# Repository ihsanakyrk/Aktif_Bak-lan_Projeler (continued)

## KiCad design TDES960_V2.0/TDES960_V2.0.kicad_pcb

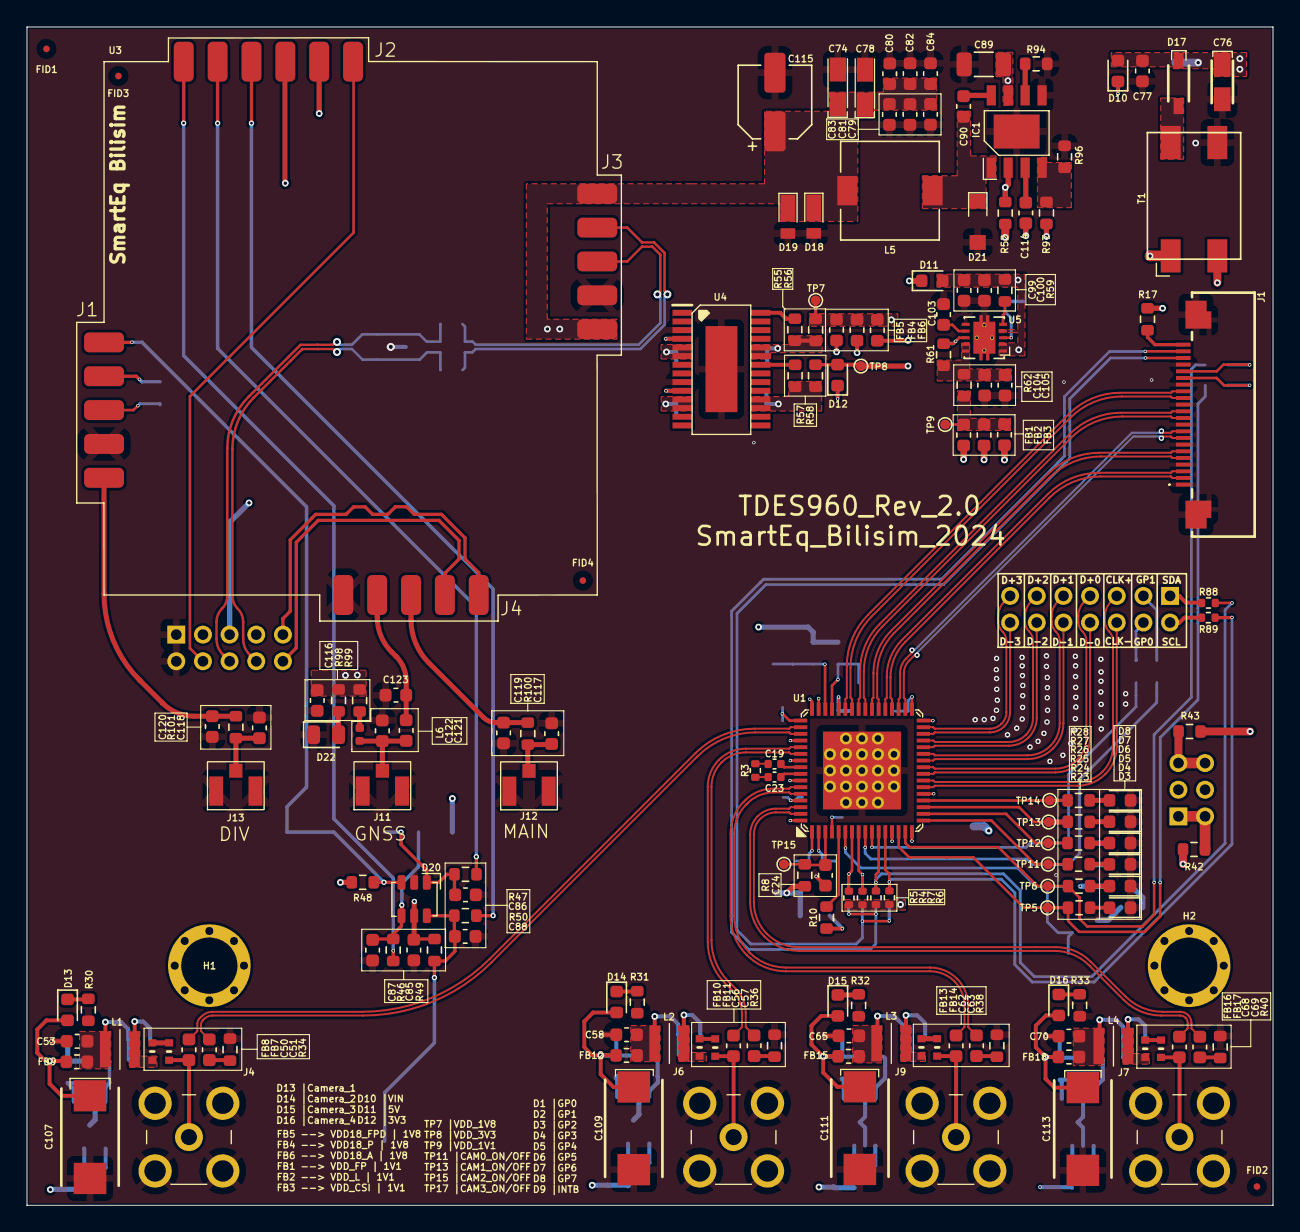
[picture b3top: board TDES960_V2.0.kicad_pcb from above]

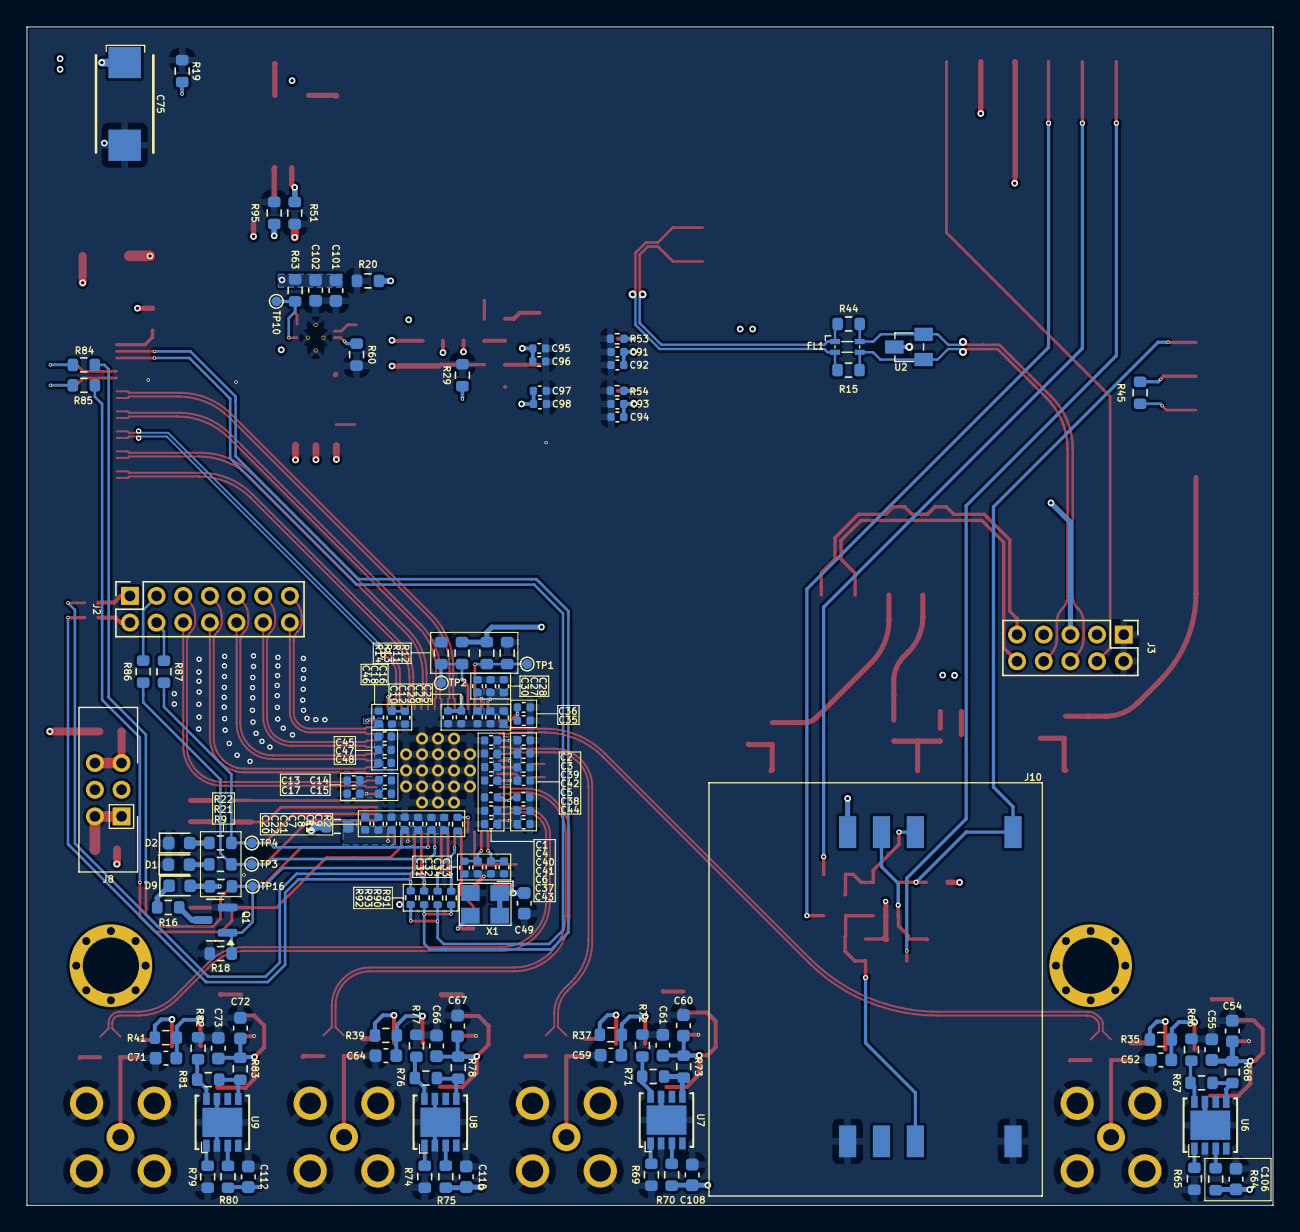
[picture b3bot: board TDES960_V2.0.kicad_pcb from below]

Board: 4 copper layers, 93.5 x 88.4 mm, 318 parts (149 on the bottom side), 184 nets.

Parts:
C1, C6, C11, C12, C17, C18, C22, C26, C29, C31, C33, C35, C39, C41, C43, C45: 0.01uF; C_0402_1005Metric
C2, C5, C9, C10, C15, C16, C19, C21, C23, C25, C30, C32, C34, C36, C40, C42, C44, C46, C95, C97: 0.1uF; C_0402_1005Metric
C3, C8, C14, C20, C28, C37, C47: 1uF; C_0402_1005Metric
C4, C7, C13, C27, C38, C48, C96, C98: 10uF; C_0402_1005Metric
C24, C105: 10uF; C_0603_1608Metric
C49, C83, C84, C85, C104, C116: 0.1uF; C_0603_1608Metric
C50, C56, C62, C68: 0.033uF/25V; C_0603_1608Metric
C51, C57, C63, C69: 0.015uF/25V; C_0603_1608Metric
C52, C54, C58, C60, C64, C66, C70, C72, C77: 0.1uF/25V; C_0603_1608Metric
C53, C55, C59, C61, C65, C67, C71, C73: 10uF/25V; C_0603_1608Metric
C74, C78: T490A107M006ATE500
C75, C107, C109, C111, C113: 22uF; CAPPM7343X310N
C76: 2.2uF; CAPPM3216X180N
C79, C80, C86, C87, C88: 33pF; C_0603_1608Metric
C81, C82: 10pF; C_0603_1608Metric
C89: 10uF; C_1206_3216Metric
C90: 100nF; C_0603_1608Metric
C91, C93: 4.7uF/10V; C_0402_1005Metric
C92, C94: 0.1uF/10V; C_0402_1005Metric
C99, C102: 4.7uF/10V; C_0603_1608Metric
C100: 0.1uF/10V; C_0603_1608Metric
C101: 1uF/10V; C_0603_1608Metric
C103: 0.01uF/10V; C_0603_1608Metric
C106, C108, C110, C112: 1uF/25V; C_0603_1608Metric
C114: 220pF; C_0603_1608Metric
C115: 100uF; CP_Elec_5x5.4
C117, C118, C119, C120, C121, C123: DNP; C_0603_1608Metric
C122: 100pF; C_0603_1608Metric
D1, D2, D3, D4, D5, D6, D7, D8, D9: LED_GREEN; LED_0603_1608Metric
D10, D11, D12: LED_RED; LED_0603_1608Metric
D13, D14, D15, D16: LED_ORANGE; LED_0603_1608Metric
D17: 1N5819HW-7-F; SOD3716X145N
D18, D19: TDZVTR5.1
D20: ESDA6V1-5SC6
D21: SS34FA
D22: LED_RED; LED_0805_2012Metric
FB1, FB2, FB3, FB4, FB5, FB6: 120ohm; 0603_Ferrite Beads
FB7, FB11, FB14, FB17: MPZ1005F470ETD25; BEADC1005X55N
FB8, FB10, FB13, FB16: MPZ1005S331ETD25; BEADC1005X55N
FB9, FB12, FB15, FB18: 1000ohm; 0603_Ferrite Beads
FID1, FID2, FID3, FID4: Fiducial; Fiducial_0.5mm_Mask1.5mm
FL1: ACM2012-900-2P-T002
H1, H2: M3x*0.5 L=6; Screw Terminal Shinbo
IC1: MP1584EN-LF-Z
J1: FFC SOCKET DR_BOTTOM 0.5MM -22P; F32R1A7H111022
J2: PinSocket_2x7_FEMALE_2.00mm; PinSocket_2x07_P2.00mm_Vertical
J3: FEMALE Through Hole Pin Header; PinHeader_2x05_P2.00mm_Vertical
J4, J6, J7, J9: XK1PWM13-ND24-Z
J8: PinSocket_2x3_FEMALE_2.00mm; Analog power connector
J10: 91228-3002; 912283002
J11, J12, J13: IPEX1-3-TXZ 214
L1, L2, L3, L4: LQH3NPN100MJR; LQH3NPN100MJRL
L5: 10uH; L_7.3x7.3_H3.5
L6: 47nH 5%; L_0402_1005Metric
Q1: BSS138; SOT-23
R1, R10, R17, R42, R43, R45, R56, R58, R62, R64, R68, R70, R73, R75, R78, R80, R83, R84, R85, R86, R87, R100, R101: 0R; R_0603_1608Metric
R2: 10K; R_0402_1005Metric
R3: 100R; R_0402_1005Metric
R4, R5, R6, R7: 4.7K; R_0402_1005Metric
R8, R12, R14, R19, R20, R29, R59: 10K; R_0603_1608Metric
R9: 4.7K; R_0603_1608Metric
R11, R13, R15, R44: DNP; R_0603_1608Metric
R16, R30, R31, R32, R33: 470R; R_0603_1608Metric
R18, R52, R55, R57, R63: 100K; R_0603_1608Metric
R21, R22, R23, R24, R25, R26, R27, R28: 220R; R_0603_1608Metric
R34, R36, R38, R40: 49.9R / %1; R_0603_1608Metric
R35, R37, R39, R41: 4.02K; R_0603_1608Metric
R46, R47, R50: 22R; R_0603_1608Metric
R48: 51K; R_0603_1608Metric
R49: 15K; R_0603_1608Metric
R51: 24.9K; R_0603_1608Metric
R53, R54, R88, R89, R90, R91: 0R; R_0402_1005Metric
R60: 4.99K/%1; R_0603_1608Metric
R61: 1.87K/%1; R_0603_1608Metric
R65, R69, R74, R79: 3.24K; R_0603_1608Metric
R66, R72, R77, R82: 5.6K/%1; R_0603_1608Metric
R67, R71, R76, R81: 34.0K/%1; R_0603_1608Metric
R92, R93: DNP; R_0402_1005Metric
R94: 200K; R_0603_1608Metric
R95: 68.1K; R_0603_1608Metric
R96: 40.2K; R_0603_1608Metric
R97: 150K; R_0603_1608Metric
R98: 1K; R_0603_1608Metric
R99: 10R; R_0603_1608Metric
T1: ACM9070-701-2PL-TL01; ACM9070
TP1, TP2, TP3, TP4, TP5, TP6, TP7, TP8, TP9, TP10, TP11, TP12, TP13, TP14, TP15, TP16: DNP; TestPoint_Pad_D0.75
U1: TDES960RTDR; QFN50P900X900X90-65N-D
U2: TPET05US3
U3: DNP; GSM_Castelled
U4: TPS767D318PWP; SOP65P640X120-29N
U5: TPS74801TDRCRQ1; VREG_TPS74801TDRCRQ1
U6, U7, U8, U9: LM2941LD_NOPB; DFN400X400X80-9N
X1: 25MHZ/100ppm/Oscillator; SMD3225-4P

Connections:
/+3V8: C74.1, C78.1, C79.1, C80.1, C81.1, C82.1, C83.1, C84.1, C115.1, C116.1, D18.1 (K), D19.1 (K), L5.2, R97.2, R98.2, R99.1, U3.17 (+3V8), U3.21 (+3V8)
/ALL_3: J8.5, J8.6, R43.2
/ALL_5: J8.1, J8.2, R42.2
/ALL_12: J8.3, T1.1IN
/ANT_DIV: C120.1, R101.2, U3.6 (ANT_DIV)
/ANT_GNSS: C122.2, C123.1, U3.4 (ANT_GNSS)
/ANT_MAIN: C119.1, R100.2, U3.3 (ANT_MAIN)
/CMLOUT_N: C23.1, R3.1
/CMLOUT_P: C19.1, R3.2
/CSI0_CLKN: J2.6, U1.22 (CSI0_CLKN)
/CSI0_CLKP: J2.5, U1.23 (CSI0_CLKP)
/CSI0_D0N: J2.8, U1.24 (CSI0_D0N)
/CSI0_D0P: J2.7, U1.25 (CSI0_D0P)
/CSI0_D1N: J2.10, U1.26 (CSI0_D1N)
/CSI0_D1P: J2.9, U1.27 (CSI0_D1P)
/CSI0_D2N: J2.12, U1.28 (CSI0_D2N)
/CSI0_D2P: J2.11, U1.29 (CSI0_D2P)
/CSI0_D3N: J2.14, U1.30 (CSI0_D3N)
/CSI0_D3P: J2.13, U1.31 (CSI0_D3P)
/CSI1_CLKN: J1.8, U1.34 (CSI1_CLKN)
/CSI1_CLKP: J1.9, U1.35 (CSI1_CLKP)
/CSI1_D0N: J1.2, U1.36 (CSI1_D0N)
/CSI1_D0P: J1.3, U1.37 (CSI1_D0P)
/CSI1_D1N: J1.5, U1.38 (CSI1_D1N)
/CSI1_D1P: J1.6, U1.39 (CSI1_D1P)
/CSI1_D2N: J1.11, U1.40 (CSI1_D2N)
/CSI1_D2P: J1.12, U1.41 (CSI1_D2P)
/CSI1_D3N: J1.14, U1.42 (CSI1_D3N)
/CSI1_D3P: J1.15, U1.43 (CSI1_D3P)
/EN3V8: IC1.2 (EN), J3.5, R51.1, R52.2
/GPIO0: R21.1, R86.1, TP3.1, U1.9 (GPIO0)
/GPIO1: R22.1, R87.1, TP4.1, U1.10 (GPIO1)
/GPIO2: R23.1, R84.1, TP5.1, U1.14 (GPIO2)
/GPIO3: R24.1, R85.1, TP6.1, U1.15 (GPIO3)
/GPIO4: R25.1, TP11.1, U1.17 (GPIO4)
/GPIO5: R26.1, TP12.1, U1.18 (GPIO5)
/GPIO6: R27.1, TP13.1, U1.19 (GPIO6)
/GPIO7: R28.1, TP14.1, U1.20 (GPIO7)
/I2C_SCL1: R4.1, R90.1, U1.8 (I2C_SCL2)
/I2C_SDA1: R5.1, R91.1, U1.7 (I2C_SDA2)
/IDX: R11.2, R12.1, TP1.1, U1.46 (IDX)
/INTB: Q1.1 (G), R9.2, R18.1, TP16.1, U1.6 (INTB)
/MODE: R13.2, R14.1, TP2.1, U1.45 (MODE)
/MODEM_NET_STATUS: J3.4, U3.16 (MODEM+NET+STATUS)
/PDB: C24.2, R8.1, TP15.1, U1.3 (PDB)
/RES: R2.2, U1.4 (RES)
/RIN0+: C50.2, U1.50 (RIN0+)
/RIN0-: C51.2, U1.51 (RIN0-)
/RIN1+: C56.2, U1.53 (RIN1+)
/RIN1-: C57.2, U1.54 (RIN1-)
/RIN2+: C62.2, U1.59 (RIN2+)
/RIN2-: C63.2, U1.60 (RIN2-)
/RIN3+: C68.2, U1.62 (RIN3+)
/RIN3-: C69.2, U1.63 (RIN3-)
/RXD: J3.10, U3.2 (RXD)
/SCL: R6.1, R89.1, R92.1, U1.12 (I2C_SCL)
/SDA: R7.1, R88.1, R93.1, U1.11 (I2C_SDA)
/TXD: J3.9, U3.1 (TXD)
/USB_GSM_N: FL1.3, J3.8, R15.1, U2.1
/USB_GSM_P: FL1.4, J3.6, R44.2, U2.2
/USB_N: FL1.2, R15.2, U3.18 (USB_N)
/USB_P: FL1.1, R44.1, U3.19 (USB_P)
/USIM_CLK: R47.1, U3.12 (USIM_CLK)
/USIM_DATA: R50.1, U3.13 (USIM_DATA)
/USIM_PRESENCE: D20.3, J10.8 (PRESENCE), R48.1, U3.10 (USIM_PRESENCE)
/USIM_RST: R46.1, U3.11 (USIM_RST)
/USIM_VDD: C85.1, D20.5, J10.6 (VCC), R49.1, U3.14 (USIM_VDD)
/VDD_EXT_1V8: R48.2, U3.15 (VDD_EXT_1V8)
/VIN: C89.1, IC1.7 (VIN), J3.3, J3.7, R52.1
/XCLK_25MHz: R10.1, U1.5 (REFCLK)
GND: C1.2, C2.2, C3.2, C4.2, C5.2, C6.2, C7.2, C8.2, C9.2, C10.2, C11.2, C12.2, C13.2, C14.2, C15.2, C16.2, C17.2, C18.2, C20.2, C21.2, C22.2, C24.1, C25.2, C26.2, C27.2, C28.2, C29.2, C30.2, C31.2, C32.2, C33.2, C34.2, C35.2, C36.2, C37.2, C38.2, C39.2, C40.2, C41.2, C42.2, C43.2, C44.2, C45.2, C46.2, C47.2, C48.2, C49.2, C52.1, C53.1, C54.1, C55.1, C58.1, C59.1, C60.1, C61.1, C64.1, C65.1, C66.1, C67.1, C70.1, C71.1, C72.1, C73.1, C74.2, C75.2, C76.2, C77.1, C78.2, C79.2, C80.2, C81.2, C82.2, C83.2, C84.2, C85.2, C86.2, C87.2, C88.2, C89.2, C91.1, C92.1, C93.1, C94.1, C95.1, C96.1, C97.1, C98.1, C99.1, C100.1, C101.1, C102.1, C103.1, C104.1, C105.1, C106.2, C107.2, C108.2, C109.2, C110.2, C111.2, C112.2, C113.2, C115.2, C116.2, C117.1, C118.1, C119.2, C120.2, C121.1, C123.2, D1.1 (K), D2.1 (K), D3.1 (K), D4.1 (K), D5.1 (K), D6.1 (K), D7.1 (K), D8.1 (K), D18.2 (A), D19.2 (A), D20.2, D21.2 (A), D22.1 (K), IC1.5 (GND), IC1.9 (EP), J1.1, J1.4, J1.7, J1.10, J1.13, J1.16, J1.19, J1.23, J1.24, J3.1, J3.2, J4.2, J4.3, J4.4, J4.5, J6.2, J6.3, J6.4, J6.5, J7.2, J7.3, J7.4, J7.5, J9.2, J9.3, J9.4, J9.5, J10.1 (GND), J10.7 (NC), J11.2, J11.3, J12.2, J12.3, J13.2, J13.3, Q1.2 (S), R2.1, R12.2, R14.2, R18.2, R19.2, R20.2, R29.2, R30.2, R31.2, R32.2, R33.2, R34.1, R36.1, R38.1, R40.1, R51.2, R53.2, R54.2, R60.2, R65.1, R66.2, R69.1, R72.2, R74.1, R77.2, R79.1, R82.2, R94.2, R95.2, R96.2, T1.2OUT, U1.65 (DAP), U2.3, U3.5 (GND), U3.7 (GND), U3.20 (GND), U4.3 (1GND), U4.9 (2GND), U4.29 (EP), U5.6 (GND), U5.11 (EXP), U6.2 (GND_2), U6.7 (GND_3), U6.9 (GND), U7.2 (GND_2), U7.7 (GND_3), U7.9 (GND), U8.2 (GND_2), U8.7 (GND_3), U8.9 (GND), U9.2 (GND_2), U9.7 (GND_3), U9.9 (GND), X1.2 (GND)
unnamed: C50.1, FB7.1, J4.1
unnamed: C51.1, R34.2
unnamed: C52.2, C53.2, FB9.2, L1.2, R35.2
unnamed: C56.1, FB11.1, J6.1
unnamed: C57.1, R36.2
unnamed: C58.2, C59.2, FB12.2, L2.2, R37.2
unnamed: C62.1, FB14.1, J9.1
unnamed: C63.1, R38.2
unnamed: C64.2, C65.2, FB15.2, L3.2, R39.2
unnamed: C68.1, FB17.1, J7.1
unnamed: C69.1, R40.2
unnamed: C70.2, C71.2, FB18.2, L4.2, R41.2
unnamed: C95.2, C96.2, R55.1, R56.2, U4.23 (1OUT), U4.24 (1OUT)
unnamed: C97.2, C98.2, R57.1, R58.2, U4.17 (2OUT), U4.18 (2OUT)
unnamed: C104.2, C105.2, R61.2, R62.2, U5.9 (OUT), U5.10 (OUT)
unnamed: C114.2, R95.1
unnamed: D1.2 (A), R21.2
unnamed: D2.2 (A), R22.2
unnamed: D3.2 (A), R23.2
unnamed: D4.2 (A), R24.2
unnamed: D5.2 (A), R25.2
unnamed: D6.2 (A), R26.2
unnamed: D7.2 (A), R27.2
unnamed: D8.2 (A), R28.2
unnamed: D9.1 (K), R16.1
unnamed: D10.1 (K), R19.1
unnamed: D11.1 (K), R20.1
unnamed: D12.1 (K), R29.1
unnamed: D13.1 (K), R30.1
unnamed: D14.1 (K), R31.1
unnamed: D15.1 (K), R32.1
unnamed: D16.1 (K), R33.1
unnamed: D17.2 (A), T1.1OUT
unnamed: C90.2, D21.1 (K), IC1.1 (SW), L5.1
unnamed: D22.2 (A), R98.1
unnamed: FB7.2, FB8.1
unnamed: FB8.2, L1.1, R35.1
unnamed: FB10.1, FB11.2
unnamed: FB10.2, L2.1, R37.1
unnamed: FB13.1, FB14.2
unnamed: FB13.2, L3.1, R39.1
unnamed: FB16.1, FB17.2
unnamed: FB16.2, L4.1, R41.1
unnamed: C90.1, IC1.8 (BST)
unnamed: C114.1, IC1.3 (COMP)
unnamed: IC1.4 (FB), R96.1, R97.1
unnamed: IC1.6 (FREQ), R94.1
unnamed: J1.17, R84.2
unnamed: J1.18, R85.2
unnamed: J1.20, R90.2, R92.2
unnamed: J1.21, R91.2, R93.2
unnamed: J1.22, R17.2
unnamed: J2.1, R88.2
unnamed: J2.2, R89.2
unnamed: J2.3, R86.2
unnamed: J2.4, R87.2
unnamed: J8.4, T1.2IN
unnamed: C86.1, D20.1, J10.4 (CLK), R47.2
unnamed: C88.1, D20.6, J10.3 (I/O), R49.2, R50.2
unnamed: C87.1, D20.4, J10.5 (RST), R46.2
unnamed: C121.2, C122.1, J11.1, L6.2
unnamed: C117.2, J12.1, R100.1
unnamed: C118.2, J13.1, R101.1
unnamed: L6.1, R99.2
unnamed: Q1.3 (D), R16.2
unnamed: C19.2, U1.56 (CMLOUTP)
unnamed: C23.2, U1.57 (CNLOUTN)
unnamed: C29.1, C30.1, U1.47 (VDD18_P1)
unnamed: C31.1, C32.1, U1.2 (VDD18_P2)
unnamed: C33.1, C34.1, U1.1 (VDD18_P3)
unnamed: R45.1, U3.8 (CTS)
unnamed: R45.2, U3.9 (RTS)
unnamed: R53.1, U4.4 (~1EN)
unnamed: R55.2, U4.28 (~1RESET)
unnamed: R54.1, U4.10 (~2EN)
unnamed: R57.2, U4.22 (~2RESET)
unnamed: R59.1, U5.5 (EN)
unnamed: R60.1, R61.1, U5.8 (FB)
unnamed: R63.1, TP10.1, U5.3 (PG)
unnamed: C103.2, U5.7 (SS)
unnamed: R66.1, R67.2, U6.8 (ADJ)
unnamed: R64.2, U6.3 (IN)
unnamed: R65.2, U6.1 (ON/OFF)
unnamed: R67.1, R68.2, U6.5 (OUT)
unnamed: R71.2, R72.1, U7.8 (ADJ)
unnamed: R70.2, U7.3 (IN)
unnamed: R69.2, U7.1 (ON/OFF)
unnamed: R71.1, R73.2, U7.5 (OUT)
unnamed: R76.2, R77.1, U8.8 (ADJ)
unnamed: R75.2, U8.3 (IN)
unnamed: R74.2, U8.1 (ON/OFF)
unnamed: R76.1, R78.2, U8.5 (OUT)
unnamed: R81.2, R82.1, U9.8 (ADJ)
unnamed: R80.2, U9.3 (IN)
unnamed: R79.2, U9.1 (ON/OFF)
unnamed: R81.1, R83.2, U9.5 (OUT)
unnamed: R10.2, X1.3 (OUT)
VDD5V: C91.2, C92.2, C93.2, C94.2, C99.2, C100.2, C101.2, C102.2, D11.2 (A), R42.1, R59.2, R63.2, U4.5 (1IN), U4.6 (1IN), U4.11 (2IN), U4.12 (2IN), U5.1 (IN), U5.2 (IN), U5.4 (BIAS)
VDD18_A: C45.1, C46.1, C47.1, C48.1, FB6.1, U1.32 (VDD18A)
VDD18_FPD: C35.1, C36.1, C37.1, C38.1, C39.1, C40.1, C41.1, C42.1, C43.1, C44.1, FB5.1, U1.49 (VDD18_FPD0), U1.55 (VDD18_FPD1), U1.58 (VDD18_FPD2), U1.64 (VDD18_FPD3)
VDD18_P: C25.1, C26.1, C27.1, C28.1, FB4.1, U1.48 (VDD18_P0)
VDDIO: C20.1, C21.1, C22.1, R1.2, U1.16 (VDDIO)
VDD_1V1: FB1.1, FB2.1, FB3.1, R62.1, TP9.1
VDD_1V8: C49.1, FB4.2, FB5.2, FB6.2, R8.2, R11.1, R13.1, R56.1, TP7.1, X1.1 (ENABLE), X1.4 (VDD)
VDD_3V3: D9.2 (A), D12.2 (A), R1.1, R4.2, R5.2, R6.2, R7.2, R9.1, R17.1, R43.1, R58.1, TP8.1
VDD_CSI: C13.1, C14.1, C15.1, C16.1, C17.1, C18.1, FB3.2, U1.21 (VDD_CSI0), U1.33 (VDD_CSI1)
VDD_EXT: C75.1, C76.1, C77.2, C106.1, C108.1, C110.1, C112.1, D10.2 (A), D17.1 (K), R64.1, R70.1, R75.1, R80.1
VDD_FP: C1.1, C2.1, C3.1, C4.1, C5.1, C6.1, FB1.2, U1.52 (VDD_FPD1), U1.61 (VDD_FPD2)
VDD_L: C7.1, C8.1, C9.1, C10.1, C11.1, C12.1, FB2.2, U1.13 (VDDL1), U1.44 (VDDL2)
VPOC0: C54.2, C55.2, C107.1, D13.2 (A), FB9.1, R68.1
VPOC1: C60.2, C61.2, C109.1, D14.2 (A), FB12.1, R73.1
VPOC2: C66.2, C67.2, C111.1, D15.2 (A), FB15.1, R78.1
VPOC3: C72.2, C73.2, C113.1, D16.2 (A), FB18.1, R83.1

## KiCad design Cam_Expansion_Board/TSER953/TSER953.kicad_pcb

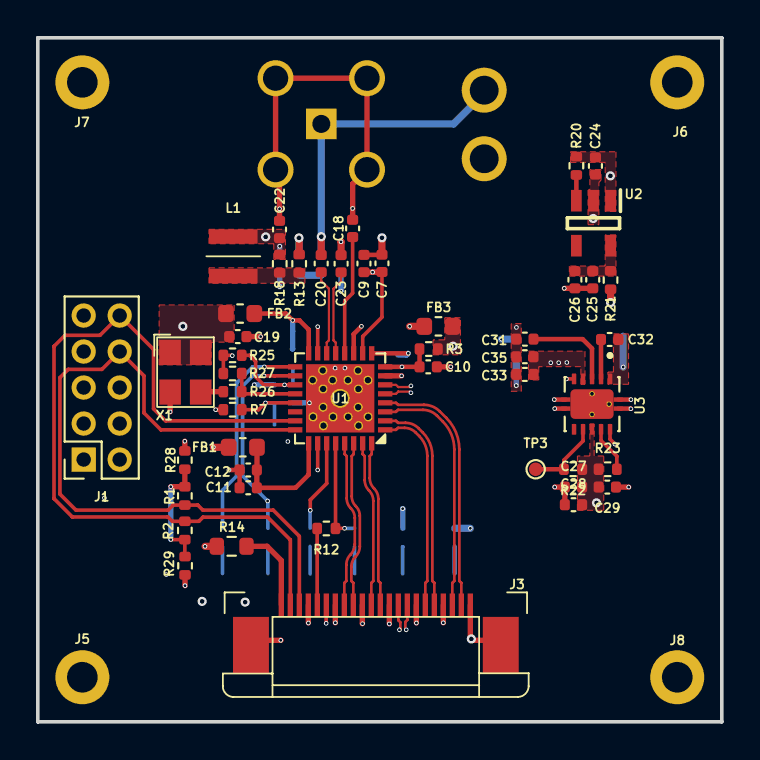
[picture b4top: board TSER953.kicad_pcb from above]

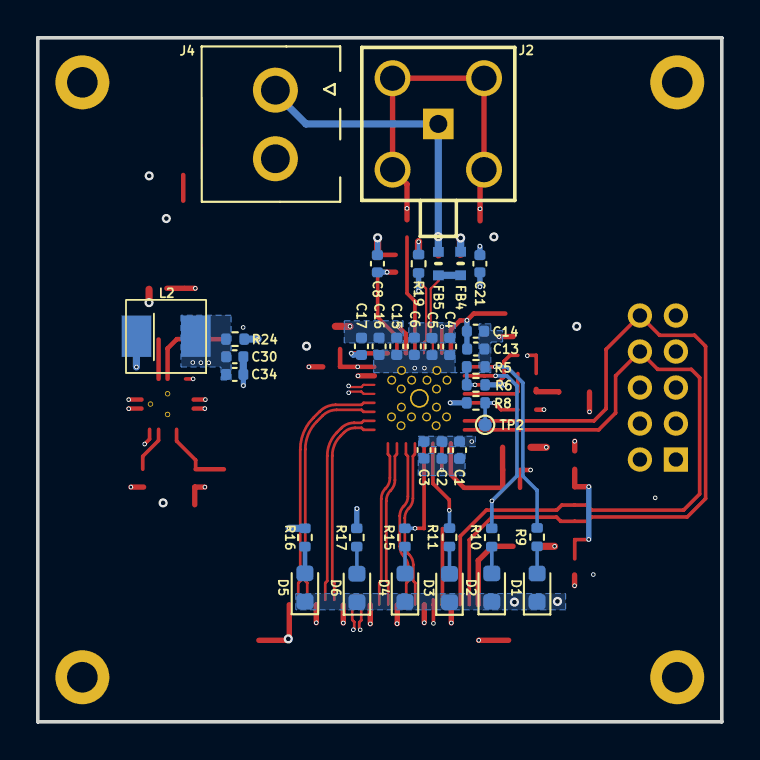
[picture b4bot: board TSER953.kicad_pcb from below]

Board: 6 copper layers, 38.0 x 38.0 mm, 90 parts (38 on the bottom side), 58 nets.

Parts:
C1, C5, C8, C10: 10uF; C_0402_1005Metric
C2, C6, C9, C12, C14, C16, C30: 0.01uF; C_0402_1005Metric
C3, C4, C7, C18, C19: 0.1uF; C_0402_1005Metric
C11, C13, C15: 1uF; C_0402_1005Metric
C17: 0.022uF; C_0402_1005Metric
C20: 0.033uF/25V; C_0402_1005Metric
C21, C22, C29, C32: 0.1uF/25V; C_0402_1005Metric
C23: 0.015uF/25V; C_0402_1005Metric
C24, C25: 1uF/10V; C_0402_1005Metric
C26, C33, C34: 10uF/10V; C_0402_1005Metric
C27: 10uF/25V; C_0402_1005Metric
C28: 4.7uF/25V; C_0402_1005Metric
C31: 1uF/25V; C_0402_1005Metric
C35: 22uF/10V; C_0402_1005Metric
D1, D2, D3, D4: LED_GREEN; LED_0603_1608Metric
D5: LED_RED; LED_0603_1608Metric
D6: LED_ORANGE; LED_0603_1608Metric
FB1, FB2, FB3: BLM18AG102SN1D; 0603_Ferrite Beads
FB4: MPZ1005S331ETD25; BEADC1005X55N
FB5: MPZ1005F470ETD25; BEADC1005X55N
J1: DNP; PinHeader_2x05_P2.00mm_Vertical
J2: 59S10H400T5Z
J3: FFC SOCKET DR_DWN 0.5MM -22P
J4: DNP; KF2EDGH-3.81-2P-Vertical
J5, J6, J7, J8: DNP; Screw
L1: LLQH3NPN100MJR; LQH3NPN100MJRL
L2: 4.7uH; MPI4040R3-4R7-R
R1, R2: 4.7K; R_0402_1005Metric
R3, R8, R16, R20, R22: 10K; R_0402_1005Metric
R5: 40.2K; R_0402_1005Metric
R6, R7, R25, R27, R29: DNP; R_0402_1005Metric
R9, R10, R11, R15: 220R; R_0402_1005Metric
R12, R13, R21, R24, R26, R28: 0R; R_0402_1005Metric
R14: 0R; R_0603_1608Metric
R17: 470R; R_0402_1005Metric
R18: 4.02K; R_0402_1005Metric
R19: 49.9R / %1; R_0402_1005Metric
R23: 100K; R_0402_1005Metric
TP2, TP3: DNP; TestPoint_Pad_D0.75
U1: TSER953RHBR; QFN50P500X500X100-33N-D
U2: LP5907MFX-1.8/NOPB; SOT95P280X145-5N
U3: LM536003QDSXRQ1; CONV_LM53600NQDSXTQ1
X1: 50MHZ/100ppm; SMD3225-4P

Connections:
/CSI_C_N: J3.15, U1.6 (CSI_CLKN)
/CSI_C_P: J3.14, U1.5 (CSI_CLKP)
/CSI_D0_N: J3.21, U1.4 (CSI_D0N)
/CSI_D0_P: J3.20, U1.3 (CSI_D0P)
/CSI_D1_N: J3.18, U1.2 (CSI_D1N)
/CSI_D1_P: J3.17, U1.1 (CSI_D1P)
/CSI_D2_N: J3.12, U1.32 (CSI_D2N)
/CSI_D2_P: J3.11, U1.31 (CSI_D2P)
/CSI_D3_N: J3.9, U1.30 (CSI_D3N)
/CSI_D3_P: J3.8, U1.29 (CSI_D3P)
/DOUT+: C20.1, U1.14 (DOUT+)
/DOUT-: C23.1, U1.13 (DOUT-)
/EXT_XVCLK: J3.6, R25.1, R27.2
/FSIN: J3.5, R12.2
/GPIO0: J1.7, R9.2, U1.17 (GPIO0)
/GPIO1: J1.5, R10.2, U1.18 (GPIO1)
/GPIO2: J1.3, R11.2, U1.27 (GPIO2)
/GPIO3: J1.1, R12.1, R15.2, U1.28 (GPIO3)
/I2C_SCL: J1.8, J3.3, R1.2, U1.24 (I2C_SCL)
/I2C_SDA: J1.10, J3.2, R2.2, U1.23 (I2C_SDA)
/IDX: R5.1, R6.2, R25.2, U1.19 (CLK_OUT/IDX)
/MODE: R7.2, R8.1, TP2.1, U1.21 (MODE)
/PDB: C10.2, J1.6, R3.1, U1.8 (PDB)
/XCLK_50MHz: R26.1, R27.1, U1.20 (CLKIN)
GND: C1.2, C2.2, C3.2, C4.2, C5.2, C6.2, C7.2, C8.2, C9.2, C10.1, C11.1, C12.2, C13.1, C14.2, C15.1, C16.2, C18.1, C19.2, C21.1, C22.1, C24.1, C25.1, C26.1, C27.1, C28.1, C29.1, C30.1, C31.1, C33.1, C34.1, C35.1, D1.1 (K), D2.1 (K), D3.1 (K), D4.1 (K), D5.1 (K), D6.1 (K), J1.4, J1.9, J2.2, J2.3, J2.4, J2.5, J3.4, J3.7, J3.10, J3.13, J3.16, J3.19, J3.22, J3.23, J3.24, J4.2, J5.1, J6.1, J7.1, J8.1, R5.2, R8.2, R19.2, U1.0 (DAP(GND)), U1.7 (RES0), U2.2 (GND), U3.5 (AGND), U3.10 (GND), U3.11 (PAD), X1.2 (GND)
unnamed: C23.2, R19.1
unnamed: D1.2 (A), R9.1
unnamed: D2.2 (A), R10.1
unnamed: D3.2 (A), R11.1
unnamed: D4.2 (A), R15.1
unnamed: D5.2 (A), R16.1
unnamed: D6.2 (A), R17.1
unnamed: FB4.1, FB5.2
unnamed: FB4.2, R13.2
unnamed: J3.1, R14.2
unnamed: C20.2, FB5.1, J2.1, J4.1
unnamed: L1.1, R13.1, R18.2
unnamed: R1.1, R2.1, R28.1, R29.1
unnamed: C17.1, U1.9 (LPF1)
unnamed: C18.2, U1.12 (LPF2)
unnamed: C7.1, C8.1, C9.1, U1.10 (VDDPLL_CAP)
unnamed: C4.1, C5.1, C6.1, U1.15 (VDDRV_CAP)
unnamed: C1.1, C2.1, C3.1, U1.26 (VDD_CAP)
unnamed: R20.2, U2.3 (EN)
unnamed: C25.2, C26.2, R21.1, U2.5 (OUT)
unnamed: C32.2, U3.2 (BOOT)
unnamed: R22.2, TP3.1, U3.7 (ENABLE)
unnamed: C30.2, C33.2, C34.2, C35.2, L2.2, R24.1, U3.4 (FB)
unnamed: C32.1, L2.1, U3.1 (SW)
unnamed: R23.2, U3.9 (SYNC/MODE)
unnamed: C31.2, U3.3 (VCC)
unnamed: R26.2, X1.3 (OUT)
VDDDRV_1V8: C13.2, C14.1, FB2.1, U1.16 (VDDDRV)
VDDD_1V8: C11.2, C12.1, FB1.1, U1.25 (VDDD)
VDD_1V8: C19.1, FB1.2, FB2.2, FB3.2, R3.2, R6.1, R7.1, R21.2, R28.2, X1.1 (ENABLE), X1.4 (VDD)
VDD_3V3: C24.2, J1.2, R14.1, R16.2, R20.1, R24.2, R29.2, U2.1 (VIN)
VDD_PLL: C15.2, C16.1, C17.2, FB3.1, U1.11 (VDDPLL)
VPOC: C21.2, C22.2, C27.2, C28.2, C29.2, L1.2, R17.2, R18.1, R22.1, R23.1, U3.8 (VIN)

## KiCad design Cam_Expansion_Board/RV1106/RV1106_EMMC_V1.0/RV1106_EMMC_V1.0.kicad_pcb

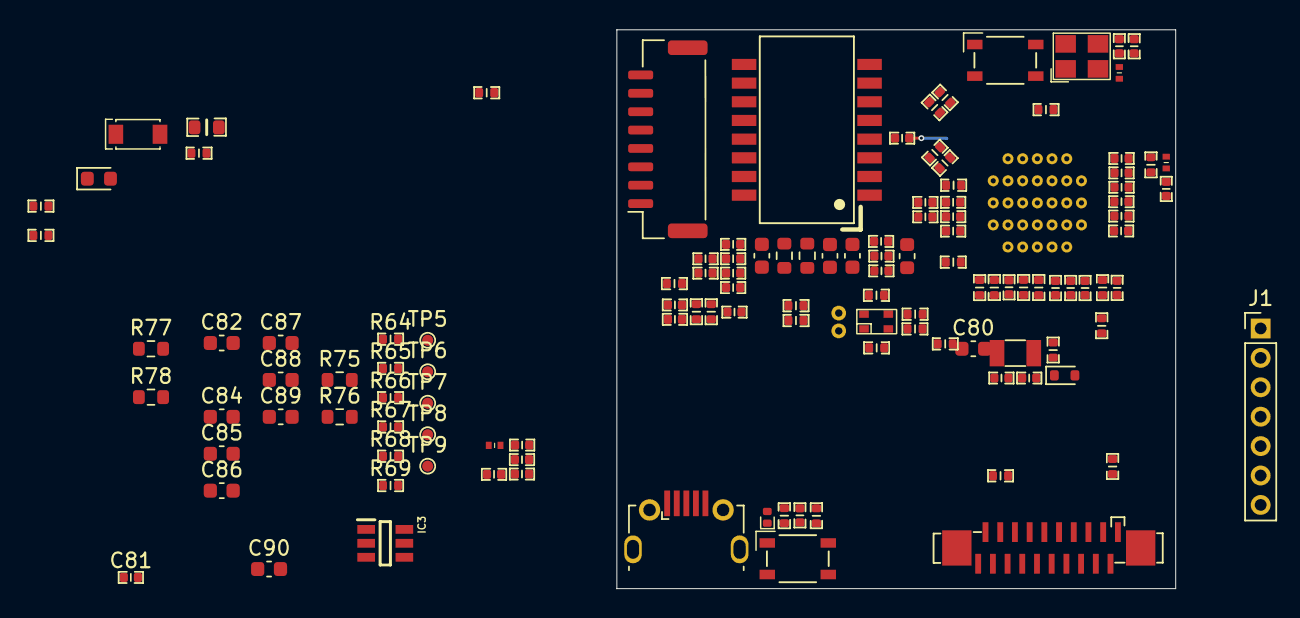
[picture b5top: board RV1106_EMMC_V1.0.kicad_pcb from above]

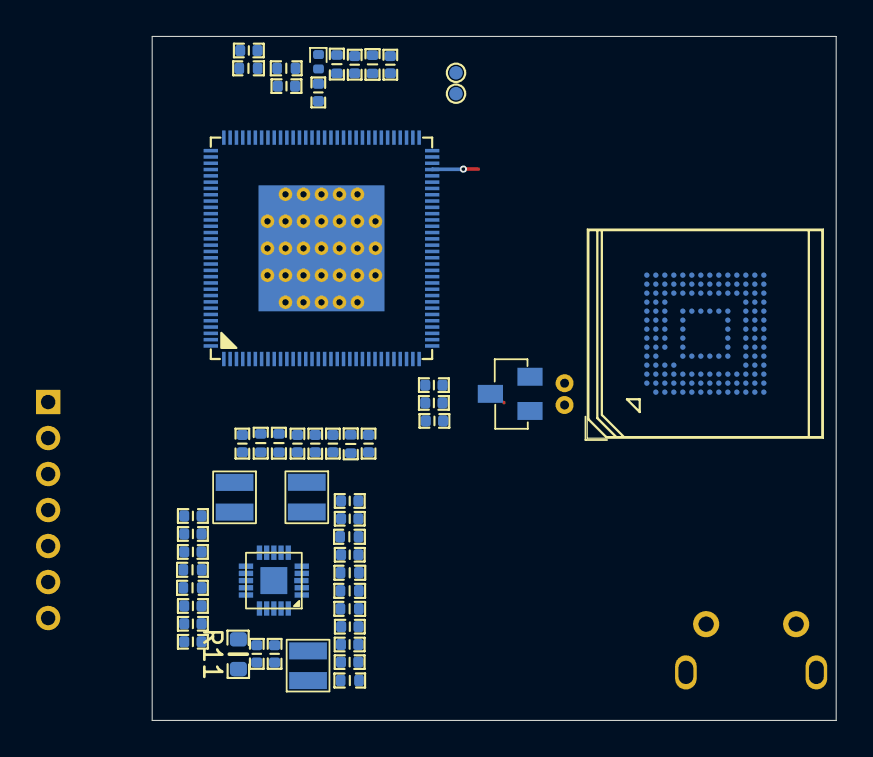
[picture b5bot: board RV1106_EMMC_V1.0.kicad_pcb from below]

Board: 6 copper layers, 38.0 x 38.0 mm, 176 parts (52 on the bottom side), 116 nets.

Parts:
C1, C2, C6, C7: 18pF 50V C0G; C_0402_1005Metric
C3, C4, C5, C9, C10, C11, C16, C17, C18, C21, C25, C27, C29, C34, C36, C50, C51, C52, C54, C55, C63, C64, C65, C66, C68, C69, C72: 100nF X5R 16V; C_0402_1005Metric
C8, C14, C15, C20, C24, C26, C62, C73: 1uF X5R 6.3V; C_0402_1005Metric
C12, C13, C19, C22, C23, C28: 10uF X5R 6.3V; C_0402_1005Metric
C35: DNP; C_0402_1005Metric
C37, C42, C45: 220pF; C_0402_1005Metric
C38, C39, C43: 4.7uF; C_0402_1005Metric
C40, C41, C44: 10uF; C_0402_1005Metric
C46, C47, C48, C49: 10uF 10V; C_0402_1005Metric
C53, C67, C70, C71: 4.7uF X5R 6.3V; C_0402_1005Metric
C74, C75: 0.01uF; C_0603_1608Metric
C76: 1000pF; C_0603_1608Metric
C77, C78, C79, C81: 1nF C0G 50V; C_0402_1005Metric
C80, C82: 10uF 25V X5R; C_0603_1608Metric
C84: 100nF; C_0603_1608Metric
C85: 22pF; C_0603_1608Metric
C86, C87: 22uF 16V X5R; C_0603_1608Metric
C88, C89, C90: 100nF 16V X5R; C_0603_1608Metric
D1: RB521S-30; D_SOD-523
D2: LED_White; LED_0603_1608Metric
D32: MBR230LSFT1G; SS14
D34, D35: ESD5451N; ESD5341N
ESD1: ESD5302F; SOT-23-Diode
FB1: DNP; SMD-4P,2.0x1.2mm
IC3: SY8113B
J1: DNP; PinHeader_1x07_P2.00mm_Vertical
J13: JST_1x8-1MP_P1.25mm_Vertical; JST_1x8_1MP_P1.25mm_Vertical
J20: MICRO XNJ ZB; Micro-B SMD
J28: AFC11-S20ICA-00
L1, L2, L7: BLM15PD121SN1; Feritte_Beads_0402
L4, L5, L6: FTC252012S1R5MBCA
L8: CBG160808U000T; 0603_Ferrite Beads
R1: 1M %5; R_0402_1005Metric
R2, R4, R6, R7, R21, R22: 22R %5; R_0402_1005Metric
R3, R28, R42: 100R %5; R_0402_1005Metric
R5, R26: 1R %5; R_0402_1005Metric
R10, R18, R25, R29, R30, R31, R32, R48, R49, R58, R62, R64, R67, R69: 0R; R_0402_1005Metric
R11: 100K %5; R_0603_1608Metric
R12, R27, R55, R56, R59, R60: 10K %5; R_0402_1005Metric
R13: 200K; R_0402_1005Metric
R14: 40.2K %1; R_0402_1005Metric
R15: 9.1K %1; R_0402_1005Metric
R16: 47K %1; R_0402_1005Metric
R17, R20: 100K %1; R_0402_1005Metric
R19: 200K %1; R_0402_1005Metric
R23: 240R %1; R_0402_1005Metric
R24: 6.04K %1; R_0402_1005Metric
R33: 1K %5; R_0402_1005Metric
R43, R44: 4.7K %5; R_0402_1005Metric
R45: DNP; R_0603_1608Metric
R46, R47: 2.2R %5; R_0402_1005Metric
R50, R61, R63, R68: DNP; R_0402_1005Metric
R57: 50K %5; R_0402_1005Metric
R65: 10K; R_0402_1005Metric
R66: 15K; R_0402_1005Metric
R70, R71: 75R; R_0603_1608Metric
R75: 110K; R_0603_1608Metric
R76: 15K; R_0603_1608Metric
R77: 120K; R_0603_1608Metric
R78: 30K; R_0603_1608Metric
S5, S6: SKRPANE010
T1: H1102NL
TP1, TP2: DNP; Test_Point
TP3, TP4, TP5, TP6, TP7, TP8, TP9: DNP; TestPoint_Pad_D0.75
U1: RV1106G3
U3: EA3036C
U7: 24MHz; SMD3225-4P
U9: RS70B08G3S03F; EMMC
Y1: Crystal_32.768kHz; Crystal_SMD_3215-2Pin_3.2x1.5mm

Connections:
/DN: ESD1.2, FB1.4, J20.2 (DM), R48.2, TP1.1
/DP: ESD1.1, FB1.1, J20.3 (DP), R49.2, TP2.1
/EMMC_CLK: R21.1, U9.M6 (CLK)
/EMMC_CMD: R56.1, U1.47 (FSPI_CS0_EMMC_CMD_GPIO4_B0_u), U9.M5 (CMD)
/EMMC_D0: R55.1, R61.1, U1.41 (FSPI_D0_EMMC_D0_GPIO4_A4_u), U9.A3 (DATA0)
/EMMC_D1: U1.42 (FSPI_D1_EMMC_D1_GPIO4_A3_u), U9.A4 (DATA1)
/EMMC_D2: U1.44 (FSPI_D2_EMMC_D2_GPIO4_A2_u), U9.A5 (DATA2)
/EMMC_D3: U1.39 (FSPI_D3_EMMC_D3_GPIO4_A6_u), U9.B2 (DATA3)
/EMMC_D4: U1.40 (SPI1_CS0_M0_I2C2_SDA_M1_UART1_TX_M2_EMM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), U9.B3 (DATA4)
/EMMC_D5: U1.38 (SPI1_CLK_M0_I2C2_SCL_M1_UART1_RX_M2_EMM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), U9.B4 (DATA5)
/EMMC_D6: U1.45 (SPI1_MOSI_M0_I2C0_SCL_M1_UART0_TX_M2_EM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), U9.B5 (DATA6)
/EMMC_D7: U1.46 (SPI1_MISO_M0_I2C0_SDA_M1_UART0_RX_M2_EM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), U9.B6 (DATA7)
/EN1: C36.1, R13.2, U3.9 (EN1)
/EN2: C35.1, R12.2, U3.8 (EN2)
/EN3: C34.1, R11.2, U3.18 (EN3)
/ETH_R_N: R32.1, U1.97 (FEPHY_RXN)
/ETH_R_P: R31.1, U1.98 (FEPHY_RXP)
/ETH_T_N: R30.1, U1.99 (FEPHY_TXN)
/ETH_T_P: R29.1, U1.100 (FEPHY_TXP)
/FLASH_ALE/EMMC_RST: R57.1, U9.K5 (RST_n)
/GPIO3_C6_d: R7.2, R50.1, U1.4 (VI_BT656_D2_M0_VI_BT1120_D10_PWM7_IR_M2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)
/GPIO4_C1_z: C79.1, R59.2, R60.1, U1.22 (PWM1_M1_SARADC_IN1_GPIO4_C1_z)
/MIPI_CSI_AVDD_1V8: C11.1, R5.2, U1.1 (MIPI_AVDD1V8_VCCIO7_VCC1V8)
/MIPI_I2C_SCL: J28.13, R43.1, U1.5 (VI_BT656_D3_M0_VI_BT1120_D11_UART5_TX_M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)
/MIPI_I2C_SDA: J28.14, R44.1, U1.7 (VI_BT656_D4_M0_VI_BT1120_D12_UART5_RX_M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)
/MIPI/LVDS_CLK_N: J28.8, U1.125 (VI_BT656_D0_M0_VI_BT1120_D8_LVDS_RX_CLK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)
/MIPI/LVDS_CLK_P: J28.7, U1.126 (VI_BT656_D1_M0_VI_BT1120_D9_LVDS_RX_CLK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)
/MIPI/LVDS_D0_N: J28.5, U1.127 (VI_BT656_CLK_M0_VI_BT1120_CLK_LVDS_RX_D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)
/MIPI/LVDS_D0_P: J28.4, U1.128 (LVDS_RX_D0P_MIPI_CSI_RX_D0P_VI_CIF_HREF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)
/MIPI/LVDS_D1_N: J28.11, U1.123 (VI_BT1120_D6_LVDS_RX_D1N_MIPI_CSI_RX_D1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)
/MIPI/LVDS_D1_P: J28.10, U1.124 (VI_BT1120_D7_LVDS_RX_D1P_MIPI_CSI_RX_D1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)
/MIPI/LVDS_MCLK0: J28.2, R6.1
/MIPI/LVDS_RST: J28.16, U1.3 (VI_CIF_VSYNC_M0_GPIO3_C5_d)
/NPOR: C78.1, R33.2, R42.1, U1.66 (nPOR)
/RECOVERY: C77.1, R27.2, R28.1, U1.23 (SARADC_IN0_GPIO4_C0_z)
/RX_P0+: R31.2, T1.6 (RD+)
/RX_P0-: R32.2, T1.8 (RD-)
/SDMMC_CLK: J1.6, R22.1
/SDMMC_CMD: J1.7, U1.16 (JTAG_LPMCU_TMS_M1_I2C0_SDA_M2_PWM11_IR_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)
/SDMMC_D0: J1.2, U1.14 (PWM8_M0_UART2_RX_M0_SDMMC_D0_GPIO3_A3_u)
/SDMMC_D1: J1.3, U1.12 (PWM9_M0_UART2_TX_M0_SDMMC_D1_GPIO3_A2_u)
/SDMMC_D2: J1.4, U1.18 (JTAG_HPMCU_TCK_M1_JTAG_CPU_TCK_M0_UART5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)
/SDMMC_D3: J1.5, U1.17 (JTAG_HPMCU_TMS_M1_JTAG_CPU_TMS_M0_UART5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)
/SDMMC_DET: J1.1, U1.11 (SDMMC_DET_GPIO3_A1_u)
/TX_P0+: R29.2, T1.1 (TD+)
/TX_P0-: R30.2, T1.3 (TD-)
/UART1_CTS: TP7.1, U1.109 (I2C4_SDA_M0_UART1_CTS_M1_VO_LCDC_D8_I2S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)
/UART1_RTS: TP6.1, U1.110 (I2C4_SCL_M0_UART1_RTS_M1_VO_LCDC_D9_I2S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)
/UART1_RX: TP8.1, U1.114 (UART1_RX_M1_VO_LCDC_D13_I2S0_SDI0_SDIO_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)
/UART1_TX: TP9.1, U1.113 (UART1_TX_M1_VO_LCDC_D12_I2S0_SDO0_SDIO_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)
/UART2_RX: TP4.1, U1.80 (JTAG_HPMCU_TMS_M0_JTAG_LPMCU_TMS_M0_JTA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)
/UART2_TX: TP3.1, U1.79 (JTAG_HPMCU_TCK_M0_JTAG_LPMCU_TCK_M0_JTA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)
/USB_DET_IN: C81.1, R65.2, R66.1, U1.25 (USB_VBUSDET)
/USB_N: R46.1, U1.26 (USB_DM)
/USB_P: R47.1, U1.27 (USB_DP)
/USB_VIN: D32.A, J20.1 (VBUS), R65.1
/VDDi: C62.1, U9.C2 (VDDi)
Earth: C80.1, C82.1, C86.1, C87.1, C88.1, C89.1, C90.1, IC3.2 (GND), R76.2, R78.2
GND: C1.2, C2.1, C3.2, C4.2, C5.2, C6.2, C7.2, C8.2, C9.2, C10.2, C11.2, C12.2, C13.2, C14.2, C15.2, C16.2, C17.2, C18.2, C19.2, C20.2, C21.2, C22.2, C23.2, C24.2, C25.2, C26.2, C27.2, C28.2, C29.2, C34.2, C35.2, C36.2, C38.1, C39.1, C40.1, C41.1, C43.1, C44.1, C46.2, C47.2, C48.2, C49.2, C50.2, C51.2, C52.2, C53.2, C54.2, C55.2, C62.2, C63.2, C64.2, C65.2, C66.2, C67.2, C68.2, C69.2, C70.2, C71.2, C72.2, C73.2, C75.2, C76.2, C77.2, C78.2, C79.2, C81.2, D2.1, D34.2, D35.2, ESD1.3, J13.7, J13.8, J13.9, J13.10, J20.5 (GND), J20.6 (Shield), J28.1, J28.3, J28.6, J28.9, J28.12, J28.15, J28.17, J28.18, J28.21, J28.22, R15.2, R17.2, R20.2, R23.2, R24.2, R25.1, R58.1, R60.2, R61.2, R66.2, S5.3, S5.4, S6.3, S6.4, TP5.1, U1.129 (ePAD), U3.1 (GND3), U3.4 (GND2), U3.5 (GND2), U3.12 (GND1), U3.13 (GND1), U3.15 (AGND), U3.17 (AGND), U3.21 (AGND), U7.2 (GND), U7.4 (GND), U9.A6 (VSS2), U9.C4 (VSS3), U9.E7 (VSS4), U9.G5 (VSS5), U9.H10 (VSS6), U9.J5 (VSS1), U9.K8 (VSSQ1), U9.N2 (VSSQ2), U9.N5 (VSSQ3), U9.P4 (VSSQ4), U9.P6 (VSSQ5)
unnamed: C74.2, C75.1
unnamed: C76.1, R70.1, R71.1
unnamed: D1.1 (K), R3.1
unnamed: D2.2, R50.2
unnamed: D32.C, R45.2
unnamed: D34.1, R28.2, S5.1, S5.2
unnamed: D35.1, R42.2, S6.1, S6.2
unnamed: FB1.2, R47.2, R49.1
unnamed: FB1.3, R46.2, R48.1
unnamed: C84.1, IC3.1 (BS)
unnamed: IC3.4 (EN), R77.2, R78.1
unnamed: C85.1, IC3.3 (FB), R75.2, R76.1
unnamed: C84.2, IC3.6 (LX)
unnamed: J28.19, J28.20, R10.1
unnamed: C74.1, T1.2 (CT1), T1.7 (CT2)
unnamed: R70.2, T1.10 (CT3)
unnamed: R71.2, T1.15 (CT4)
unnamed: C6.1, U1.21 (OSC_RTC_XIN), Y1.1
unnamed: C7.1, U1.20 (OSC_RTC_XOUT), Y1.2
unnamed: C2.2, R1.1, U1.68 (OSC_SOC_XIN), U7.1 (X1)
unnamed: R1.2, R2.2, U1.69 (OSC_SOC_XOUT)
unnamed: L1.1, U1.96 (OTP_AVDD1V8_ETH_AVDD1V8_TSADC_AVDD1V8)
unnamed: C8.1, R3.2, U1.19 (RTC_AVDD3V3)
unnamed: R58.2, U1.57 (TVSS)
unnamed: R21.2, U1.48 (FSPI_CLK_EMMC_CLK_GPIO4_B1_d)
unnamed: R22.2, U1.15 (JTAG_LPMCU_TCK_M1_I2C0_SCL_M2_PWM10_M0_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)
unnamed: C50.1, R64.2, U1.43 (VCCIO3_VCC)
unnamed: R4.2, U1.85 (I2C3_SCL_M1_AUD_DSM_N_UART5_TX_M1_PWM11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)
unnamed: R6.2, U1.2 (MIPI_CLK0_OUT_VI_CIF_CLKO_M0_GPIO3_C4_d)
unnamed: R62.2, R63.2, U1.108 (VCCIO5_VCC)
unnamed: R67.2, R68.2, U1.88 (VCCIO6_VCC)
unnamed: R25.2, U1.37 (CODEC_AVSS)
unnamed: C53.1, U1.30 (CODEC_VCM)
unnamed: R23.1, U1.52 (DRAM_ZQ)
unnamed: L7.2, U1.101 (FEPHY_AVDD3V3)
unnamed: R24.1, U1.102 (FEPHY_REXT)
unnamed: C54.1, R26.2, U1.24 (SARADC_USB_AVDD1V8)
unnamed: C37.2, R14.1, R15.1, U3.14 (FB1)
unnamed: C42.2, R16.1, R17.1, U3.3 (FB2)
unnamed: C45.2, R19.1, R20.1, U3.2 (FB3)
unnamed: L5.2, U3.6 (LX2)
unnamed: L6.2, U3.20 (LX3)
unnamed: L4.2, U3.11 (LX)
unnamed: C1.1, R2.1, U7.3 (X2)
RX0_N: J13.6, T1.9 (RX-)
RX0_P: J13.3, T1.11 (RX+)
TRD0_N: J13.2, T1.14 (TX-)
TRD0_P: J13.1, T1.16 (TX+)
VCC1V8_CODEC: C28.1, C29.1, L2.2, U1.31 (CODEC_AVDD1V8)
VCC5V0_SYS: C46.1, C47.1, C48.1, C49.1, C85.2, C86.2, C87.2, C88.2, C89.2, R11.1, R12.1, R13.1, R45.1, R75.1, U3.7 (VIN2), U3.10 (VIN1), U3.16 (VCC), U3.19 (VIN3)
VCCIO_FLASH: C63.1, C64.1, C65.1, C66.1, C67.1, R55.2, R56.2, R57.2, R64.1, R69.1, U9.C6 (VCCQ1), U9.M4 (VCCQ2), U9.N4 (VCCQ3), U9.P3 (VCCQ4), U9.P5 (VCCQ5)
VCC_1V8: C3.1, C4.1, C26.1, C27.1, C71.1, C72.1, L1.2, L2.1, L8.1, R5.1, R26.1, R27.1, R43.2, R44.2, R59.1, R63.1, R68.1, U1.53 (DDR_PLL_AVDD1V8), U1.70 (OSC_AVDD1V8_PLL_AVDD1V8)
VCC_3V3: C9.1, C10.1, C37.1, C38.2, C39.2, C51.1, C52.1, C55.1, C68.1, C69.1, C70.1, D1.2 (A), L4.1, L7.1, R10.2, R14.2, R33.1, R62.1, R67.1, R69.2, U1.13 (VCCIO4_VCC), U1.28 (USB_AVDD3V3), U1.61 (PMU_VCC3V3), U1.81 (VCCIO1_VCC3V3), U9.E6 (VCC1), U9.F5 (VCC2), U9.J10 (VCC3), U9.K9 (VCC4)
VCC_DDR: C22.1, C23.1, C24.1, C25.1, C43.2, C44.2, C45.1, C73.1, L6.1, L8.2, R19.2, U1.49 (DDR_VDDQ_1), U1.50 (DDR_VDDQ_2), U1.56 (DDR_VDDQ_3)
VDD_0V9: C5.1, C12.1, C13.1, C14.1, C15.1, C16.1, C17.1, C18.1, C40.2, C41.2, C42.1, L5.1, R16.2, R18.1, U1.10 (DVDD_1), U1.51 (DVDD_2), U1.54 (DVDD_3), U1.55 (DVDD_4), U1.67 (OSC_DVDD0V9_PMU_DVDD0V9), U1.71 (PLL_DVDD0V9), U1.82 (DVDD_5), U1.103 (DVDD_6), U1.116 (DVDD_7)
VDD_ARM: C19.1, C20.1, C21.1, R18.2, U1.115 (CPU_DVDD)
VIN: C80.2, C82.2, C90.2, IC3.5 (IN), J13.4, J13.5, R77.1
